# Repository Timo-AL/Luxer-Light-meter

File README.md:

# Lux-Light-meter
A light meter designed for taking photo（用于摄影的测光表）

## 如何制作

LMG2MB_gerber文件夹里面的zip去找板厂下单，建议嘉立创哑光黑阻焊，减少反光影响

LMG2MV_BOM.xlsx 对照采购原件，尤其注意type-c封装

R11限流电阻根据情况使用，我用的VA 3.3V的1602，选的0欧

安装luattool v2，下载库中的LuatOS-SoC_V0007_AIR103.soc和main.lua

调节旋钮，使液晶屏字符清晰，最好用陶瓷螺丝刀，小心短路

## 如何使用

B1 电源开关

B2 模式选择，长按在A（光圈优先），S（快门优先），L（低感光度光圈优先），I（感光度设置）模式之间切换

R1 曝光补偿旋钮

R2 参数旋钮

D1 电池电压，低于3.4时需要充电

D2 曝光误差，误差大于0.3EV时显示+，小于-0.3EV显示减号，大于±1EV显示E，小于±0.3EV显示=

D3 ISO值

D4 工作模式

D4 快门速度，速度低于1S会以“秒数"”格式显示

D6 光圈

D7 曝光补偿，设置感光度时该位置显示低感值

## 下载固件

按如图所示线序与CH340串口模块连接，TX和RX需要交叉，不连接VCC

按如图所示方法下载固件，开始下载后打开打开测光表电源

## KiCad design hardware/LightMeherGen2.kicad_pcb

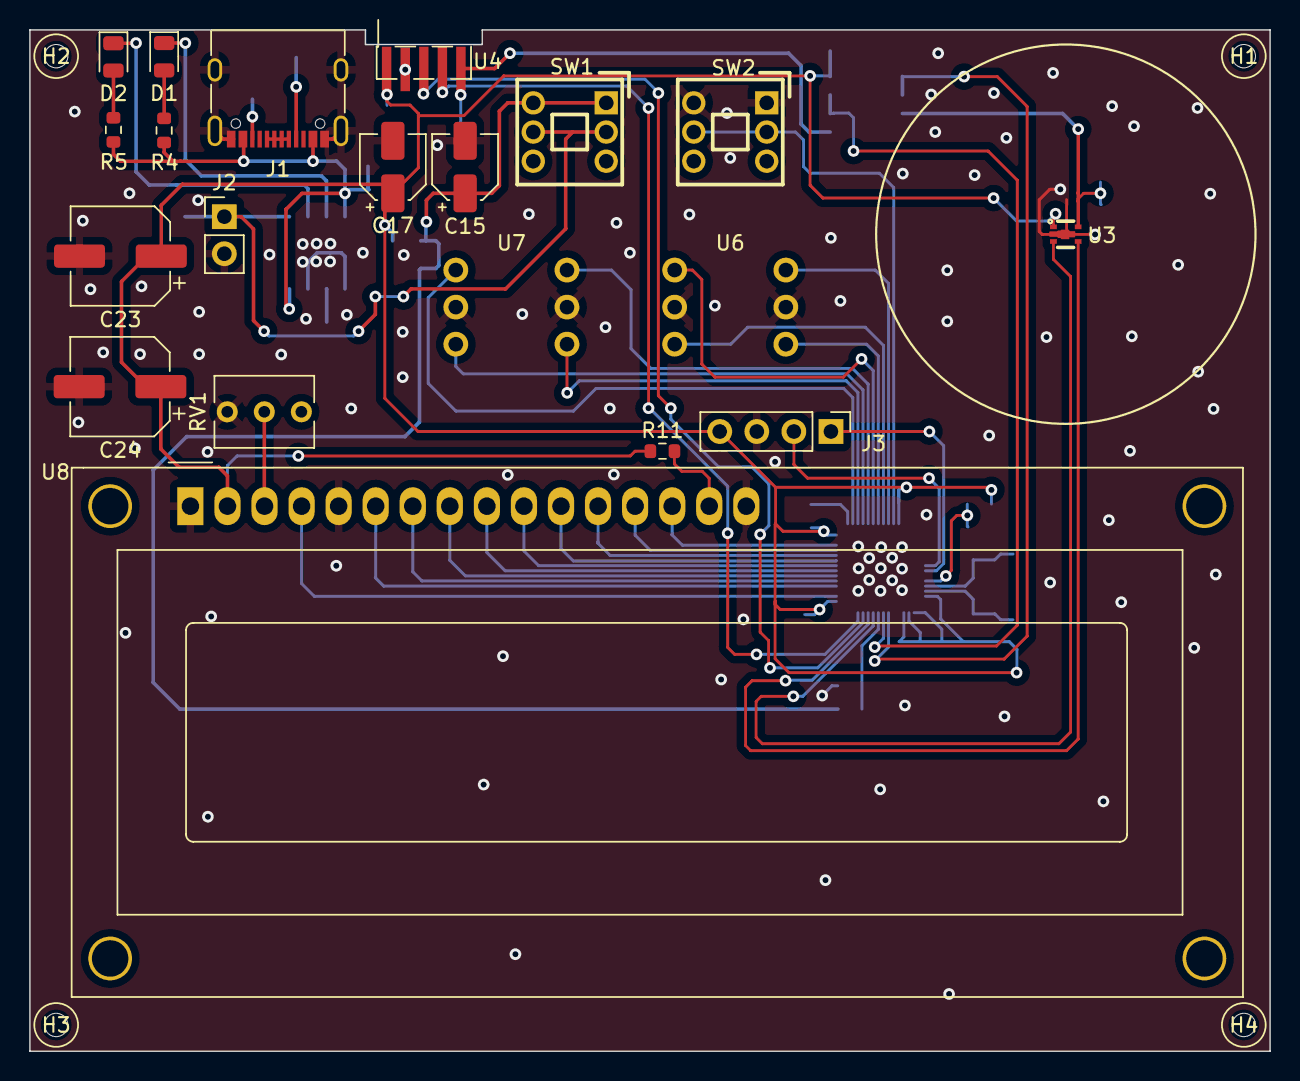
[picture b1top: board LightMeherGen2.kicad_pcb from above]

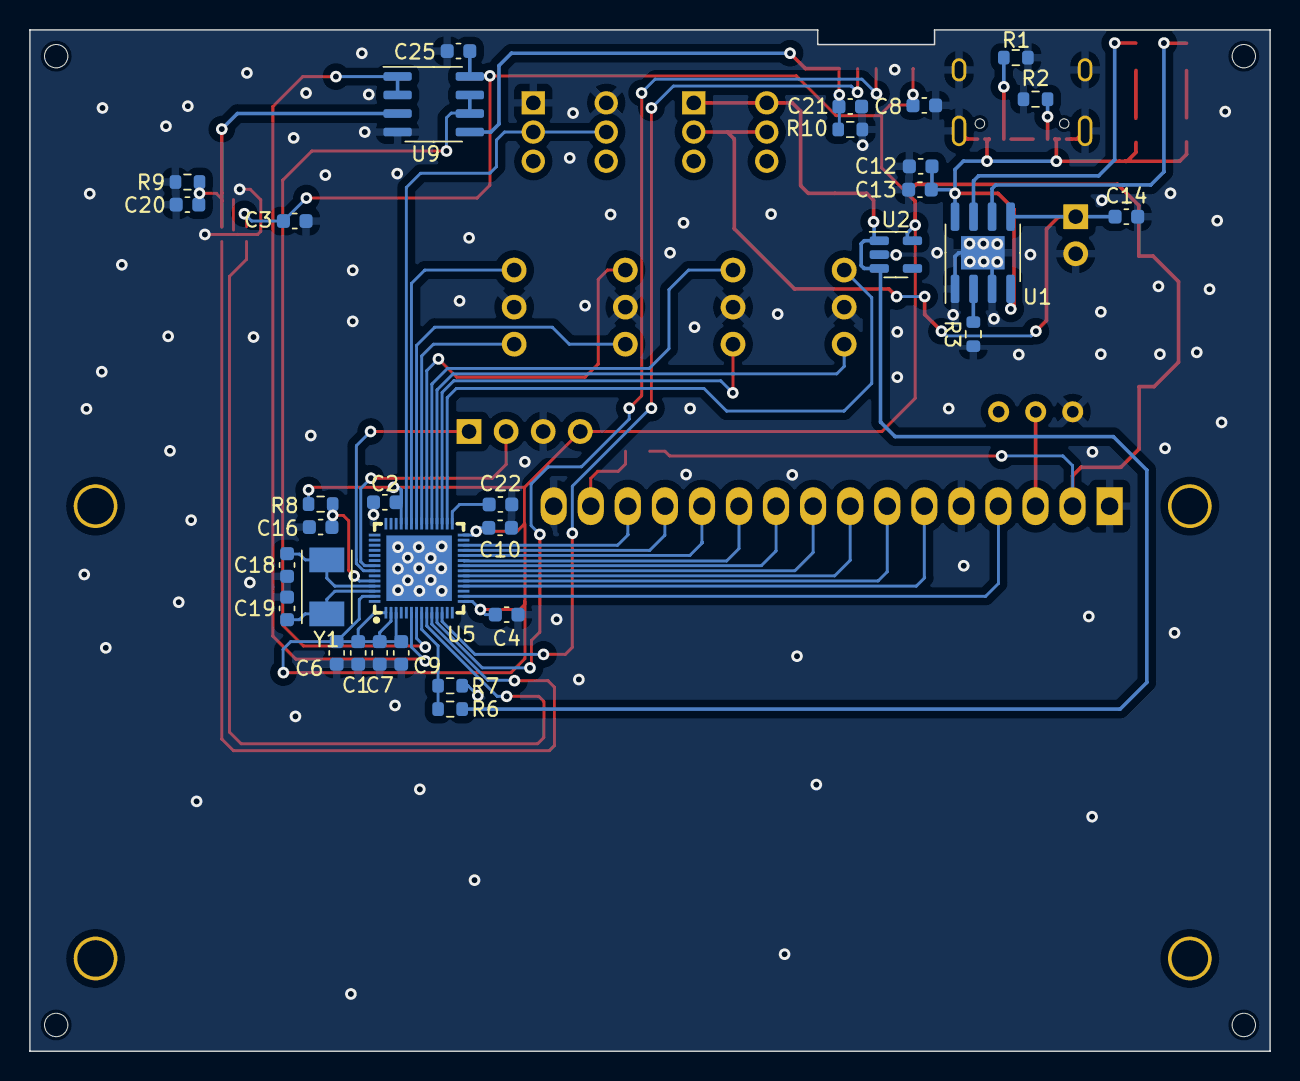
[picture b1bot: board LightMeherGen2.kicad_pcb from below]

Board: 2 copper layers, 85.0 x 70.0 mm, 56 parts (32 on the bottom side), 49 nets.

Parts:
C1, C2, C3, C4, C6, C7, C8, C9, C10, C16, C25: 100nf; C_0603_1608Metric
C12, C14, C22: 10uf; C_0603_1608Metric
C13: 100nF; C_0603_1608Metric
C15, C17: 10uf; CP_Elec_4x4.5
C18, C19, C20, C21: 20pf; C_0603_1608Metric
C23, C24: 100uf; CP_Elec_6.3x5.4
D1, D2: LED; LED_0805_2012Metric
H1, H2, H3, H4: MountingHole; MH_M1.5
J1: USB_C_Receptacle_USB2.0; USB_C_Receptacle_XKB_U262-16XN-4BVC11
J2: Conn_01x02; PinHeader_1x02_P2.54mm_Vertical
J3: Conn_01x04; PinHeader_1x04_P2.54mm_Vertical
R1, R2: 5.1K; R_0603_1608Metric
R3: 1.2K; R_0603_1608Metric
R4, R5: 200; R_0603_1608Metric
R6, R7: 10k; R_0603_1608Metric
R8: 1k; R_0603_1608Metric
R9: 4.22k; R_0603_1608Metric
R10: 4.22K; R_0603_1608Metric
R11: 510; R_0603_1608Metric
RV1: 10k; Potentiometer_Vishay_T73XW_Horizontal
SW1, SW2: XKB7070-Z; SW-TH_6P-L7.0-W7.0-P2.00
U1: TP4056; SOIC-8-1EP_3.9x4.9mm_P1.27mm_EP2.29x3mm
U2: LN1134-3.3; SOT-23-5
U3: BH1620FVC-TR; WSOF-5_L1.6-W1.2-P0.50-TL
U4: BH1620FVC-TR; PinHeader_1x05_P1.27mm_Vertical_SMD_Pin1Right
U5: AIR103_CORE_QFN; QFN-56_L6.0-W6.0-P0.35-BL-EP4.7
U6, U7: BCD8421_3-3
U8: RC1602A; WC1602A
U9: LMC6482; SOIC-8_3.9x4.9mm_P1.27mm
Y1: 40MHz; Crystal_SMD_TXC_7A-2Pin_5x3.2mm

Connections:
+5V: C12.2, C13.2, J1.A4 (VBUS), J1.A9 (VBUS), J1.B4 (VBUS), J1.B9 (VBUS), R4.2, R5.2, U1.4 (VCC), U1.8 (CE)
/RX: J3.2, U5.07 (U0_RX)
/TX: J3.1, U5.08 (U0_TX)
GND: C1.2, C2.2, C3.2, C4.2, C6.2, C7.2, C8.2, C9.2, C10.2, C12.1, C13.1, C14.2, C15.2, C16.2, C17.2, C18.2, C19.2, C20.2, C21.2, C22.2, C23.2, C24.2, C25.2, J1.A1 (GND), J1.A12 (GND), J1.B1 (GND), J1.B12 (GND), J1.S1 (SHIELD), J2.2, J3.3, R1.1, R2.1, R3.1, R7.2, R9.2, R10.2, RV1.1, SW2.1, SW2.4, U1.1 (TEMP), U1.3 (GND), U1.9 (EXPAD), U2.2 (GND), U3.2 (GND), U4.2 (GND), U5.57 (EXPDA), U6.2 (C), U6.5 (C), U7.2 (C), U7.5 (C), U8.1 (VSS), U8.5 (R/W), U8.16 (K), U9.4 (V-)
unnamed: D1.2 (A), R4.1
unnamed: D1.1 (K), U1.7 (CHRG)
unnamed: D2.2 (A), R5.1
unnamed: D2.1 (K), U1.6 (STDBY)
unnamed: J1.A5 (CC1), R1.2
unnamed: J1.B5 (CC2), R2.2
unnamed: J1.A6 (D+), J1.A7 (D-), J1.B6 (D+), J1.B7 (D-)
unnamed: C14.1, J2.1, SW1.2, SW1.5, U1.5 (BATT)
unnamed: R3.2, U1.2 (PROG)
unnamed: C15.1, R6.1, SW1.1, SW1.4, U2.1 (VIN), U2.3 (ON/~OFF)
unnamed: U3.3 (GC1), U5.23 (PA_05)
unnamed: U3.4 (GC2), U5.24 (PA_06)
unnamed: C20.1, R9.1, U3.5 (IOUT), U9.3 (+)
unnamed: U4.3 (GC1), U5.25 (PA_07)
unnamed: U4.4 (GC2), U5.26 (PA_08)
unnamed: C21.1, R10.1, U4.5 (IOUT), U9.5 (+)
unnamed: C22.1, U5.43 (CAP)
unnamed: U5.20 (PA_02), U9.1, U9.2 (-)
unnamed: U5.21 (PA_03), U9.6 (-), U9.7
unnamed: R6.2, R7.1, U5.22 (PA_04)
unnamed: U5.30 (PA_11), U8.4 (RS)
unnamed: U5.32 (PA_13), U8.6 (E)
unnamed: U5.33 (PA_14), U8.7 (DB0)
unnamed: U5.34 (PA_15), U8.8 (DB1)
unnamed: U5.35 (PB_00), U8.9 (DB2)
unnamed: U5.36 (PB_01), U8.10 (DB3)
unnamed: U5.37 (PB_02), U8.11 (DB4)
unnamed: U5.38 (PB_03), U8.12 (DB5)
unnamed: U5.40 (PB_04), U8.14 (DB7)
unnamed: U5.44 (PB_06), U7.1
unnamed: U5.45 (PB_07), U7.4 (2)
unnamed: U5.46 (PB_08), U7.3 (4)
unnamed: U5.47 (PB_09), U7.6 (8)
unnamed: SW2.2, SW2.5, U5.52 (PB_10)
unnamed: U5.48 (PB_12), U6.1
unnamed: U5.49 (PB_13), U6.4 (2)
unnamed: U5.50 (PB_14), U6.3 (4)
unnamed: U5.51 (PB_15), U6.6 (8)
unnamed: U5.39 (PB_27), U8.13 (DB6)
unnamed: C16.1, R8.2, U5.10 (RESTET)
unnamed: C19.1, U5.12 (XTAL_IN), Y1.1
unnamed: C18.1, U5.11 (XTAL_OUT), Y1.2
unnamed: R11.2, U8.15 (A/VEE)
unnamed: RV1.2, U8.3 (VO)
VCC: C1.1, C2.1, C3.1, C4.1, C6.1, C7.1, C8.1, C9.1, C10.1, C17.1, C23.1, C24.1, C25.1, J3.4, R8.1, R11.1, U2.5 (VOUT), U3.1 (VCC), U4.1 (VCC), U5.13 (VDD33), U5.15 (VDD33), U5.16 (VDD33), U5.17 (VDD33), U5.29 (VDD33), U5.42 (VDD33), U5.53 (VDD33), U8.2 (VDD), U9.8 (V+)

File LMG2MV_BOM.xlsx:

Date: | 44677.762916666667
Tool: | Eeschema (6.99.0-1665-g4ee6cfe5b6)
Generator: | C:\Program Files\KiCad\6.99\bin\scripting\plugins/bom_csv_grouped_by_value_with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
Component Count: | 56
Ref | Qnty | Value | Footprint | Description | Vendor
C1, C2, C3, C4, C6, C7, C8, C9, C10, C16, C25, | 11 | 100nf | Capacitor_SMD:C_0603_1608Metric
C12, C14, C22, | 3 | 10uf | Capacitor_SMD:C_0603_1608Metric
C13, | 1 | 100nF | Capacitor_SMD:C_0603_1608Metric
C15, C17, | 2 | 10uf | Capacitor_SMD:CP_Elec_4x4.5
C18, C19, C20, C21, | 4 | 20pf | Capacitor_SMD:C_0603_1608Metric
C23, C24, | 2 | 100uf | Capacitor_SMD:CP_Elec_6.3x5.4
D1, D2, | 2 | LED | LED_SMD:LED_0805_2012Metric
J1, | 1 | USB_C_Receptacle_USB2.0 | Connector_USB:USB_C_Receptacle_XKB_U262-16XN-4BVC11
J3, | 1 | Conn_01x04 | Connector_PinHeader_2.54mm:PinHeader_1x04_P2.54mm_Vertical
R1, R2, | 2 | 5.1K | Resistor_SMD:R_0603_1608Metric
R3, | 1 | 1.2K | Resistor_SMD:R_0603_1608Metric
R4, R5, | 2 | 200 | Resistor_SMD:R_0603_1608Metric
R6, R7, | 2 | 10k | Resistor_SMD:R_0603_1608Metric
R8, | 1 | 1k | Resistor_SMD:R_0603_1608Metric
R9, R10, | 1 | 4.22k | Resistor_SMD:R_0603_1608Metric | 精度千分之一
R11, | 1 | 510 | Resistor_SMD:R_0603_1608Metric
RV1, | 1 | 10k | Potentiometer_THT:Potentiometer_Vishay_T73XW_Horizontal | 调整对比度的时候手一定要稳，惨痛教训
SW1, SW2, | 2 | XKB7070-Z | FP:SW-TH_6P-L7.0-W7.0-P2.00
U1, | 1 | TP4056 | Package_SO:SOIC-8-1EP_3.9x4.9mm_P1.27mm_EP2.29x3mm
U2, | 1 | ME6211C33 | Package_TO_SOT_SMD:SOT-23-5
U3, | 1 | BH1620FVC-TR | FP:WSOF-5_L1.6-W1.2-P0.50-TL
U4, | 1 | BH1620FVC-TR | FP:PinHeader_1x05_P1.27mm_Vertical_SMD_Pin1Right
U5, | 1 | AIR103_CORE_QFN | FP:QFN-56_L6.0-W6.0-P0.35-BL-EP4.7
U6, U7, | 2 | BCD8421_3-3 | FP:BCD8421_3-3
U8, | 1 | RC1602A | Display:WC1602A | 推荐使用VA屏，对比度高
U9, | 1 | LMC6482 | Package_SO:SOIC-8_3.9x4.9mm_P1.27mm
Y1, | 1 | 40MHz | Crystal:Crystal_SMD_TXC_7A-2Pin_5x3.2mm
J2 | 1 | 803040电池
 | 1 | 余弦修正器 |  | 就是光照传感器的盖子，外径25mm左右

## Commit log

2020-02-24 Rename BOM_中文.md to 物料表_中文.md
2022-04-26 Delete BOM_物料表 directory
    rm
2022-04-26 Delete PCB directory
    rm
2022-04-26 Delete model_模型 directory
    rm
2022-04-26 Add files via upload
    new version
2022-04-26 readme
